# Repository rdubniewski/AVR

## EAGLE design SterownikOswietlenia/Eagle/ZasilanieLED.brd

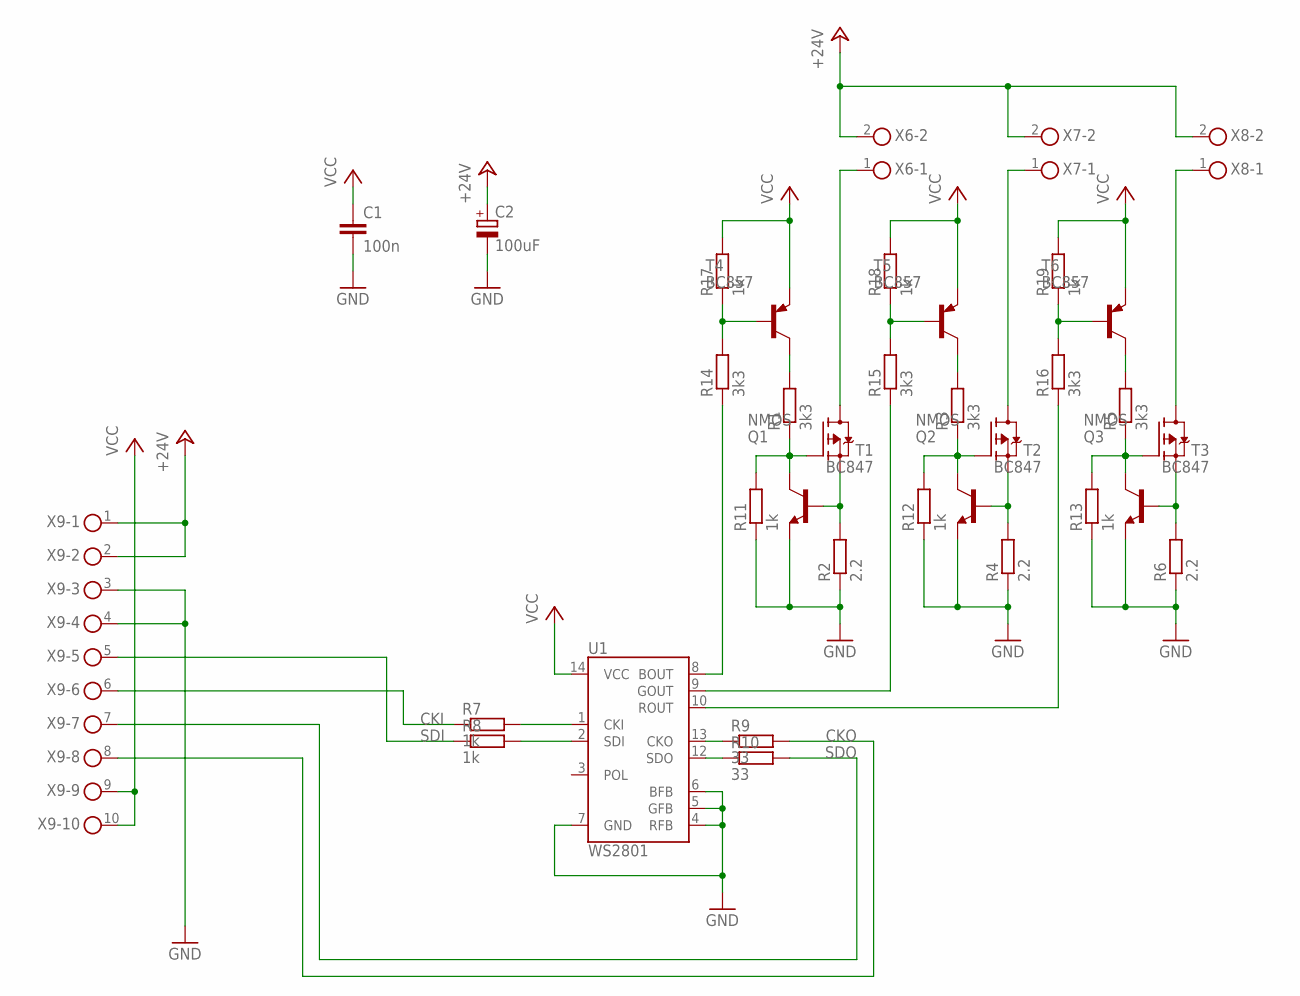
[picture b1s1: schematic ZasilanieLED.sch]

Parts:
C1: 100n; C1206
C2: 100uF; E5-10,5
Q1, Q2, Q3: NMOS; TO252
R1, R3, R5, R14, R15, R16: 3k3; R1206
R2, R4, R6: 2.2; 0207/10
R7, R8, R11, R12, R13, R17, R18, R19: 1k; R1206
R9, R10: 33; R1206
T1, T2, T3: BC847; SOT23
T4, T5, T6: BC857; SOT23-BEC
U1: WS2801; SOP-14
X6, X7, X8: AKL59-02; 2POL35
X9: AKL59-10; 10POL35

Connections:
+24V: C2.+, X6.2, X7.2, X8.2, X9.1, X9.2
CKI: R7.1, X9.6
CKO: R9.2, X9.8
GND: C1.2, C2.-, R2.1, R4.1, R6.1, R11.1, R12.1, R13.1, T1.2 (E), T2.2 (E), T3.2 (E), U1.4 (RFB), U1.5 (GFB), U1.6 (BFB), U1.7 (GND), X9.3, X9.4
unnamed: R7.2, U1.1 (CKI)
unnamed: R8.2, U1.2 (SDI)
unnamed: R9.1, U1.13 (CKO)
unnamed: R14.1, U1.8 (BOUT)
unnamed: R15.1, U1.9 (GOUT)
unnamed: R16.1, U1.10 (ROUT)
unnamed: Q1.2 (S), R2.2, T1.1 (B)
unnamed: Q2.2 (S), R4.2, T2.1 (B)
unnamed: Q3.2 (S), R6.2, T3.1 (B)
unnamed: R10.1, U1.12 (SDO)
unnamed: Q1.3 (D), X6.1
unnamed: Q2.3 (D), X7.1
unnamed: Q3.3 (D), X8.1
unnamed: R1.2, T4.C
unnamed: R3.2, T5.C
unnamed: R5.2, T6.C
unnamed: Q1.1 (G), R1.1, R11.2, T1.3 (C)
unnamed: Q2.1 (G), R3.1, R12.2, T2.3 (C)
unnamed: Q3.1 (G), R5.1, R13.2, T3.3 (C)
unnamed: R14.2, R17.1, T4.B
unnamed: R15.2, R18.1, T5.B
unnamed: R16.2, R19.1, T6.B
SDI: R8.1, X9.5
SDO: R10.2, X9.7
VCC: C1.1, R17.2, R18.2, R19.2, T4.E, T5.E, T6.E, U1.14 (VCC), X9.9, X9.10

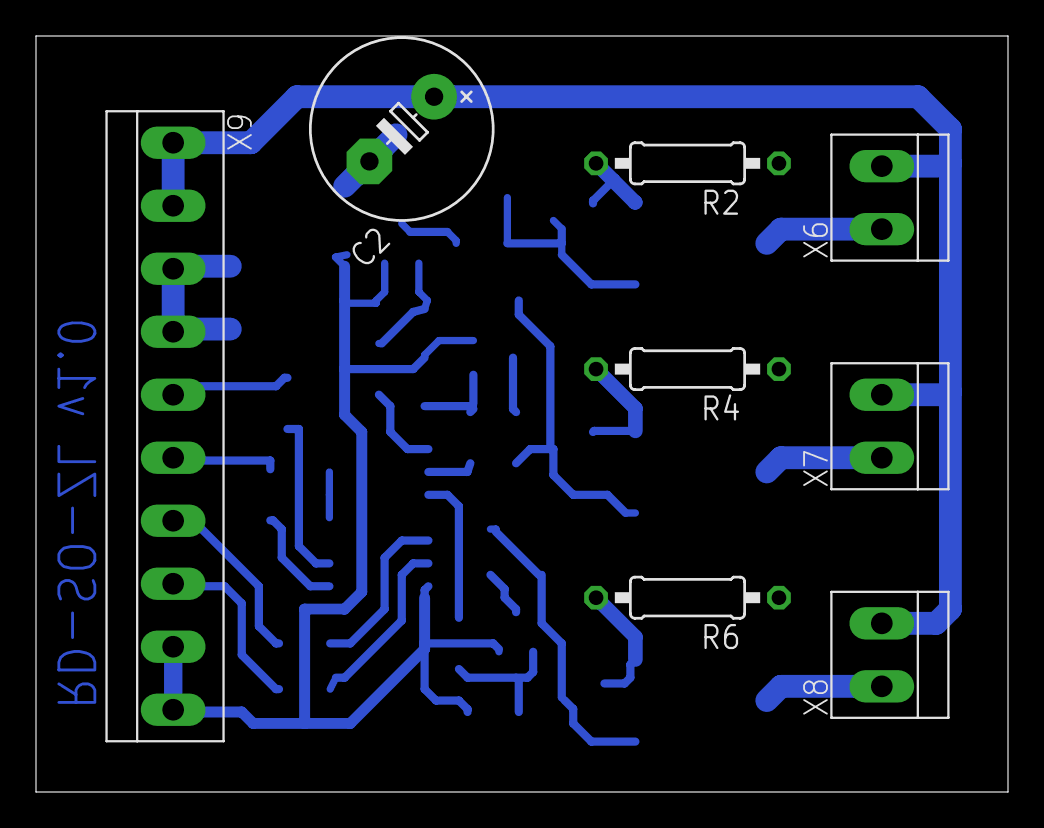
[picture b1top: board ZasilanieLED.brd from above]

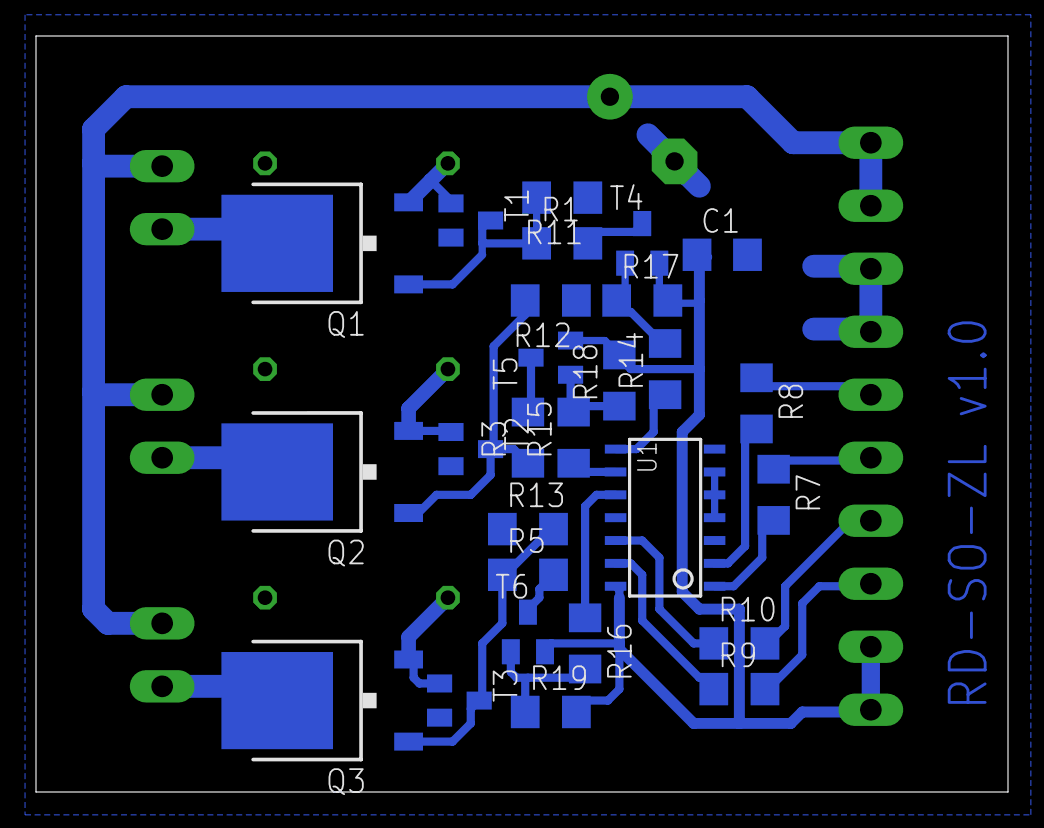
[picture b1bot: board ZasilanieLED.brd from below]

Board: 2 copper layers, 54.0 x 42.0 mm, 35 parts (27 on the bottom side), 29 nets.

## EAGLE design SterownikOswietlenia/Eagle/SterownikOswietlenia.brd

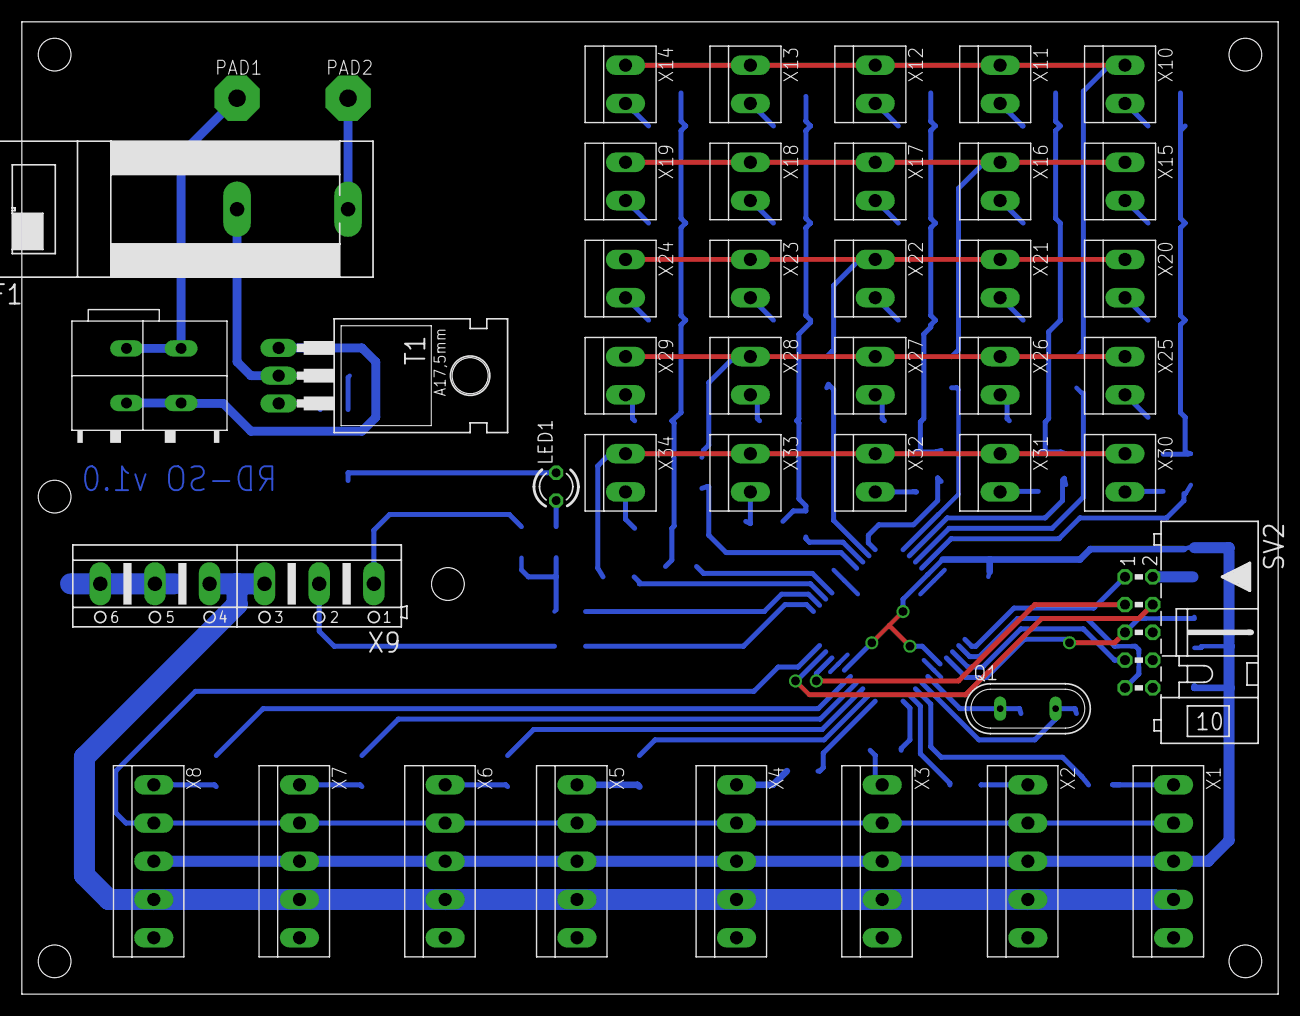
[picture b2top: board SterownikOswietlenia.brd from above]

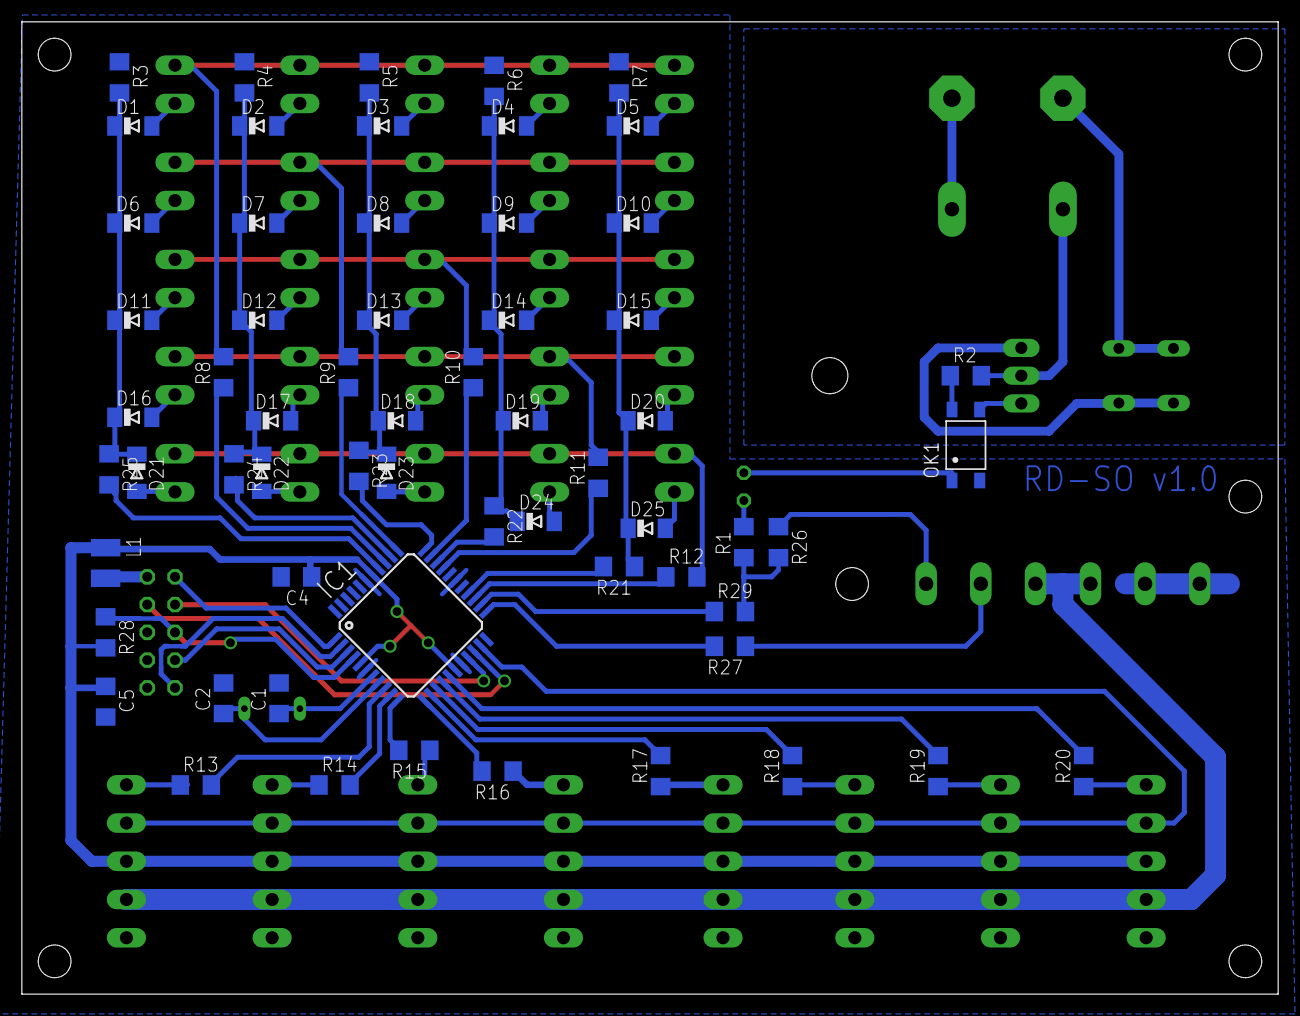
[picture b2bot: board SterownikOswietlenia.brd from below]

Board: 2 copper layers, 115.0 x 89.0 mm, 103 parts (61 on the bottom side), 87 nets.

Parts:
C1, C2: 22p; C1206
C4, C5: 100n; C1206
D1, D2, D3, D4, D5, D6, D7, D8, D9, D10, D11, D12, D13, D14, D15, D16, D17, D18, D19, D20, D21, D22, D23, D24, D25: 1N4148; MINIMELF
F1: 100mA; F457
IC1: MEGA32-A; TQFP44
L1: 100u; R1210
LED1: RED; LED3MM
OK1: TLP161J; MFP4
PAD1, PAD2: WIREPAD4,16O1,6; 4,16O1,6
Q1: 12MHz; QS
R1, R2, R8, R9, R10, R11, R12, R13, R14, R15, R16, R17, R18, R19, R20, R21, R22, R23, R24, R25, R26, R27, R29: 100; R1206
R3, R4, R5, R6, R7: 1k; R1206
R28: 10k; R1206
SV2: KANDA; ML10L
T1: BT138-H; TO220BH
U$1: AK3001-2
X1, X2, X3, X4, X5, X6, X7, X8: 5POL35
X9: AK500/6
X10, X11, X12, X13, X14, X15, X16, X17, X18, X19, X20, X21, X22, X23, X24, X25, X26, X27, X28, X29, X30, X31, X32, X33, X34: 2POL35

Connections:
+5V: L1.2, SV2.2
+24V: X1.4, X2.4, X3.4, X4.4, X5.4, X6.4, X7.4, X8.4, X9.3, X9.4
BTN-H-0: IC1.36, R8.1
BTN-H-1: IC1.34, R9.1
BTN-H-2: IC1.32, R10.1
BTN-H-3: IC1.30, R11.1
BTN-H-4: IC1.25, R12.1
BTN-V-0: IC1.37, R25.2
BTN-V-1: IC1.35, R24.2
BTN-V-2: IC1.33, R23.2
BTN-V-3: IC1.31, R22.2
BTN-V-4: IC1.26, R21.2
GND: C1.2, C2.2, C4.2, C5.2, IC1.6, IC1.18, IC1.28, IC1.39, OK1.3, R3.1, R4.1, R5.1, R6.1, R7.1, SV2.8, SV2.10, X1.5, X2.5, X3.5, X4.5, X5.5, X6.5, X7.5, X8.5, X9.5, X9.6
I2C-SCL: IC1.19, SV2.3
I2C-SDA: IC1.20, SV2.4
ISP-MISO: IC1.2, SV2.9
ISP-MOSI: IC1.1, SV2.1
ISP-SCK: IC1.3, SV2.7
LED-CKO-0: IC1.9, R13.2
LED-CKO-1: IC1.10, R14.2
LED-CKO-2: IC1.11, R15.2
LED-CKO-3: IC1.12, R16.2
LED-CKO-4: IC1.13, R17.2
LED-CKO-5: IC1.14, R18.2
LED-CKO-6: IC1.15, R19.2
LED-CKO-7: IC1.16, R20.2
LED-POWER: R1.1, R26.2, R29.2
LED-SDO: IC1.21, X1.2, X2.2, X3.2, X4.2, X5.2, X6.2, X7.2, X8.2
M$44: R12.2, X30.1, X31.1, X32.1, X33.1, X34.1
unnamed: PAD1.1, U$1.P$3, U$1.P$4
unnamed: OK1.6, R2.1
unnamed: F1.1, R2.2, T1.T2
unnamed: OK1.4, T1.G
unnamed: LED1.K, OK1.1
unnamed: LED1.A, R1.2
unnamed: R13.1, X1.1
unnamed: T1.T1, U$1.P$1, U$1.P$2
unnamed: D1.A, X10.2
unnamed: D2.A, X11.2
unnamed: F1.2, PAD2.1
unnamed: D3.A, X12.2
unnamed: D4.A, X13.2
unnamed: R14.1, X2.1
unnamed: R15.1, X3.1
unnamed: R16.1, X4.1
unnamed: R17.1, X5.1
unnamed: D5.A, X14.2
unnamed: D10.A, X19.2
unnamed: D9.A, X18.2
unnamed: D8.A, X17.2
unnamed: D7.A, X16.2
unnamed: D6.A, X15.2
unnamed: D11.A, X20.2
unnamed: D12.A, X21.2
unnamed: D13.A, X22.2
unnamed: D14.A, X23.2
unnamed: D15.A, X24.2
unnamed: D20.A, X29.2
unnamed: D19.A, X28.2
unnamed: D17.A, X26.2
unnamed: D16.A, X25.2
unnamed: D21.A, X30.2
unnamed: D22.A, X31.2
unnamed: D23.A, X32.2
unnamed: D24.A, X33.2
unnamed: D25.A, X34.2
unnamed: R18.1, X6.1
unnamed: R8.2, X10.1, X11.1, X12.1, X13.1, X14.1
unnamed: R9.2, X15.1, X16.1, X17.1, X18.1, X19.1
unnamed: R10.2, X20.1, X21.1, X22.1, X23.1, X24.1
unnamed: R11.2, X25.1, X26.1, X27.1, X28.1, X29.1
unnamed: R19.1, X7.1
unnamed: R20.1, X8.1
unnamed: C1.1, IC1.7, Q1.1
unnamed: C2.1, IC1.8, Q1.2
unnamed: R27.1, X9.2
unnamed: R26.1, X9.1
unnamed: IC1.24, R29.1
unnamed: D18.A, X27.2
unnamed: D5.C, D10.C, D15.C, D20.C, D25.C, R7.2, R21.1
unnamed: D4.C, D9.C, D14.C, D19.C, D24.C, R6.2, R22.1
unnamed: D3.C, D8.C, D13.C, D18.C, D23.C, R5.2, R23.1
unnamed: D2.C, D7.C, D12.C, D17.C, D22.C, R4.2, R24.1
unnamed: D1.C, D6.C, D11.C, D16.C, D21.C, R3.2, R25.1
POWER-IO-0: IC1.23, R27.2
RESET: IC1.4, R28.1, SV2.5
VCC: C4.1, C5.1, IC1.5, IC1.17, IC1.38, L1.1, R28.2, X1.3, X2.3, X3.3, X4.3, X5.3, X6.3, X7.3, X8.3

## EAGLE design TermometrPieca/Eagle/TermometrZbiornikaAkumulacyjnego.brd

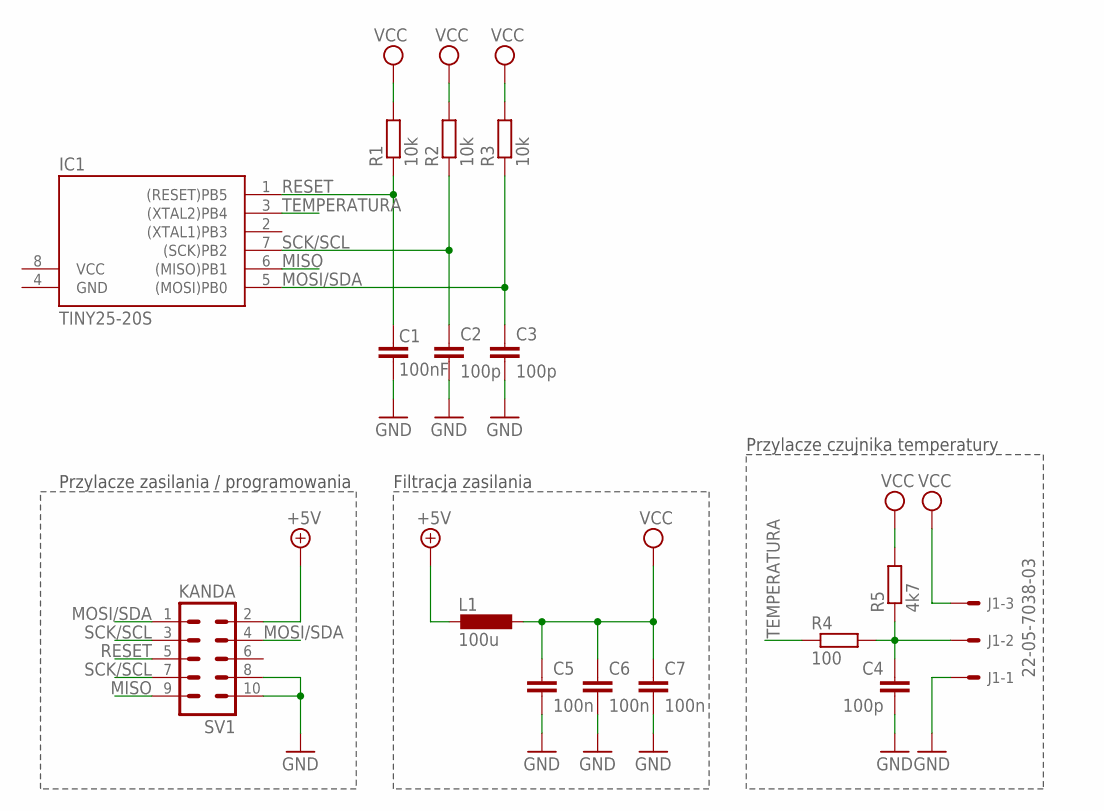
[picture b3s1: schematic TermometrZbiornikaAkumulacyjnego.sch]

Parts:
C1: 100nF; C1206
C2, C3, C4: 100p; C1206
C5, C6, C7: 100n; C1206
IC1: TINY25-20S; SOIC8
J1: 22-05-7038-03; 7395-03
L1: 100u; R1210
R1, R2, R3: 10k; R1206
R4: 100; R1206
R5: 4k7; R1206
SV1: KANDA; ML10L

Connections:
+5V: L1.2, SV1.2
GND: C1.2, C2.2, C3.2, C4.2, C5.2, C6.2, C7.2, IC1.4 (GND), J1.1, SV1.8, SV1.10
MISO: IC1.6 ((MISO)PB1), SV1.9
MOSI/SDA: C3.1, IC1.5 ((MOSI)PB0), R3.1, SV1.1, SV1.4
unnamed: C4.1, J1.2, R4.2, R5.1
RESET: C1.1, IC1.1 ((RESET)PB5), R1.1, SV1.5
SCK/SCL: C2.1, IC1.7 ((SCK)PB2), R2.1, SV1.3, SV1.7
TEMPERATURA: IC1.3 ((XTAL2)PB4), R4.1
VCC: C5.1, C6.1, C7.1, IC1.8 (VCC), J1.3, L1.1, R1.2, R2.2, R3.2, R5.2

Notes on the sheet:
Filtracja zasilania
Przylacze czujnika temperatury
Przylacze zasilania / programowania

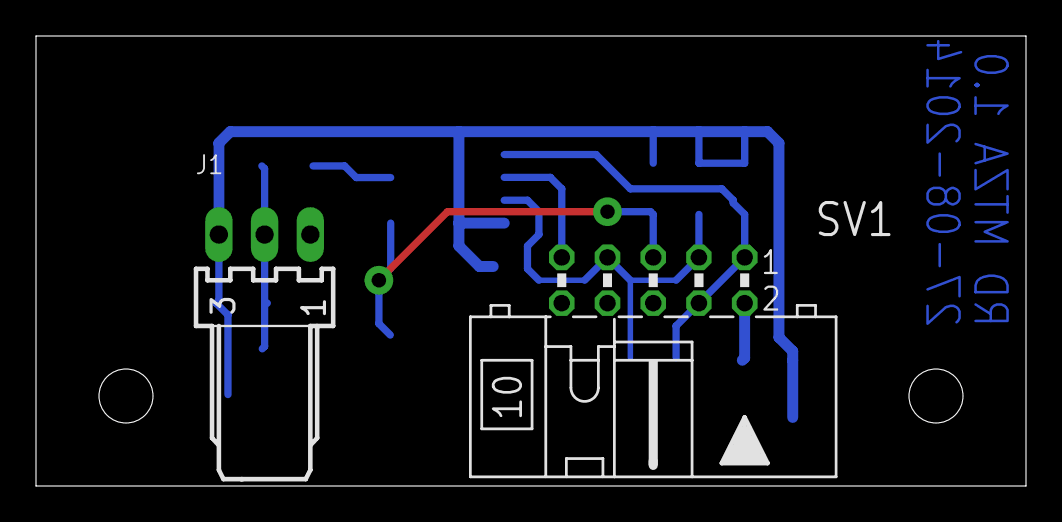
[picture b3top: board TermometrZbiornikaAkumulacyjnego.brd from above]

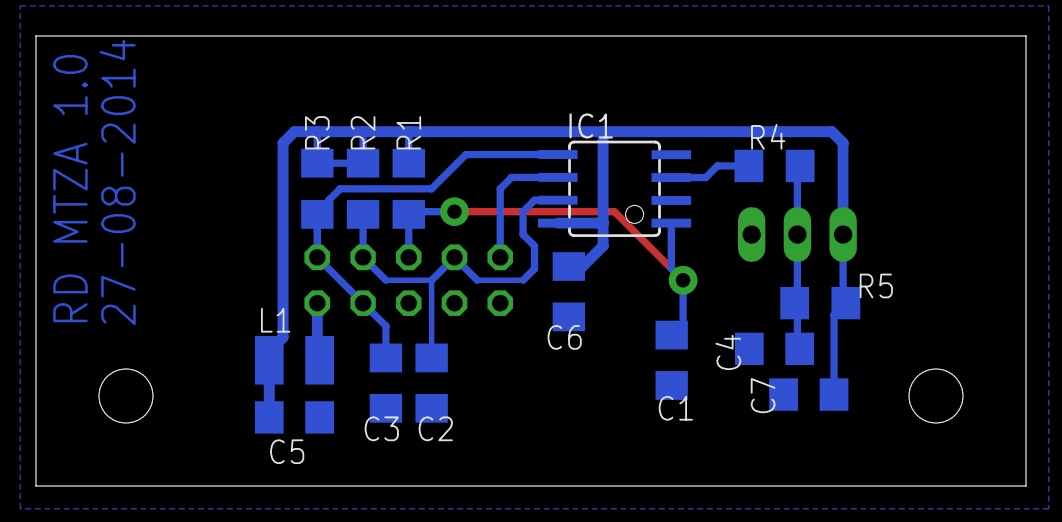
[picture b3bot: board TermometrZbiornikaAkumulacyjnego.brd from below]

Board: 2 copper layers, 55.0 x 25.0 mm, 16 parts (14 on the bottom side), 9 nets.

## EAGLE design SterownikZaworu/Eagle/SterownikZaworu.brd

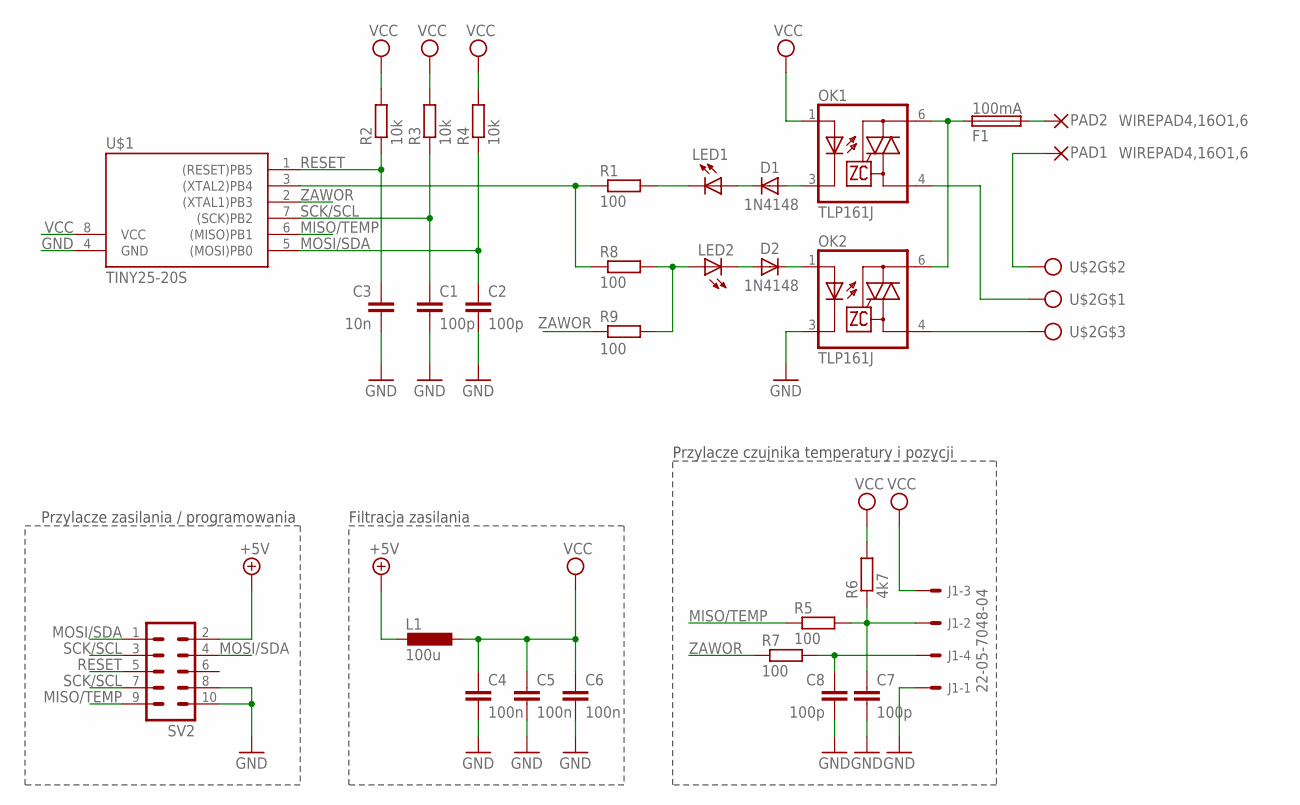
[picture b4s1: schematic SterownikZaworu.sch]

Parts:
C1, C2, C7, C8: 100p; C1206
C3: 10n; C1206
C4, C5, C6: 100n; C1206
D1, D2: 1N4148; MINIMELF
F1: 100mA; F457
J1: 22-05-7048-04; 7395-04
L1: 100u; R1210
LED1, LED2: LED3MM
OK1, OK2: TLP161J; MFP4
PAD1, PAD2: WIREPAD4,16O1,6; 4,16O1,6
R1, R5, R7, R8, R9: 100; R1206
R2, R3, R4: 10k; R1206
R6: 4k7; R1206
SV2: ML10L
U$1: TINY25-20S; SOIC8
U$2: AK3001-3

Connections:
+5V: L1.2, SV2.2
GND: C1.2, C2.2, C3.2, C4.2, C5.2, C6.2, C7.2, C8.2, J1.1, OK2.3 (C), SV2.8, SV2.10, U$1.4 (GND)
MISO/TEMP: R5.1, SV2.9, U$1.6 ((MISO)PB1)
MOSI/SDA: C2.1, R4.1, SV2.1, SV2.4, U$1.5 ((MOSI)PB0)
unnamed: PAD1.1, U$2.P$3, U$2.P$4
unnamed: C7.1, J1.2, R5.2, R6.1
unnamed: F1.1, OK1.6 (A2), OK2.6 (A2)
unnamed: D1.A, OK1.3 (C)
unnamed: D1.C, LED1.A
unnamed: LED1.K (C), R1.2
unnamed: R1.1, R8.1, U$1.3 ((XTAL2)PB4)
unnamed: OK1.4 (A1), U$2.P$1, U$2.P$2
unnamed: OK2.4 (A1), U$2.P$5, U$2.P$6
unnamed: C8.1, J1.4, R7.2
unnamed: F1.2, PAD2.1
unnamed: LED2.A, R8.2, R9.1
unnamed: D2.A, LED2.K (C)
unnamed: D2.C, OK2.1 (A)
RESET: C3.1, R2.1, SV2.5, U$1.1 ((RESET)PB5)
SCK/SCL: C1.1, R3.1, SV2.3, SV2.7, U$1.7 ((SCK)PB2)
VCC: C4.1, C5.1, C6.1, J1.3, L1.1, OK1.1 (A), R2.2, R3.2, R4.2, R6.2, U$1.8 (VCC)
ZAWOR: R7.1, R9.2, U$1.2 ((XTAL1)PB3)

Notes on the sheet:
Filtracja zasilania
Przylacze czujnika temperatury i pozycji
Przylacze zasilania / programowania

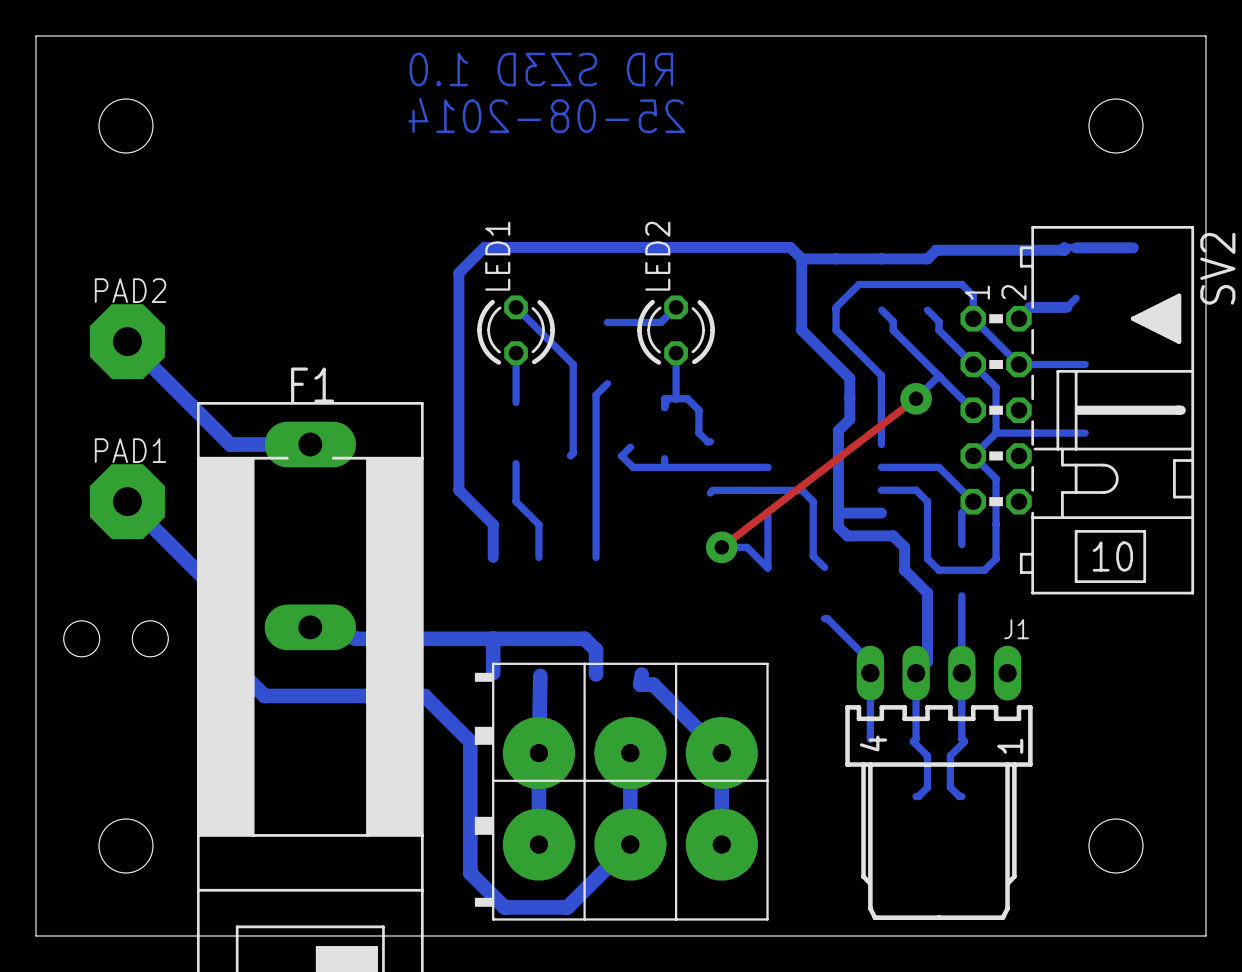
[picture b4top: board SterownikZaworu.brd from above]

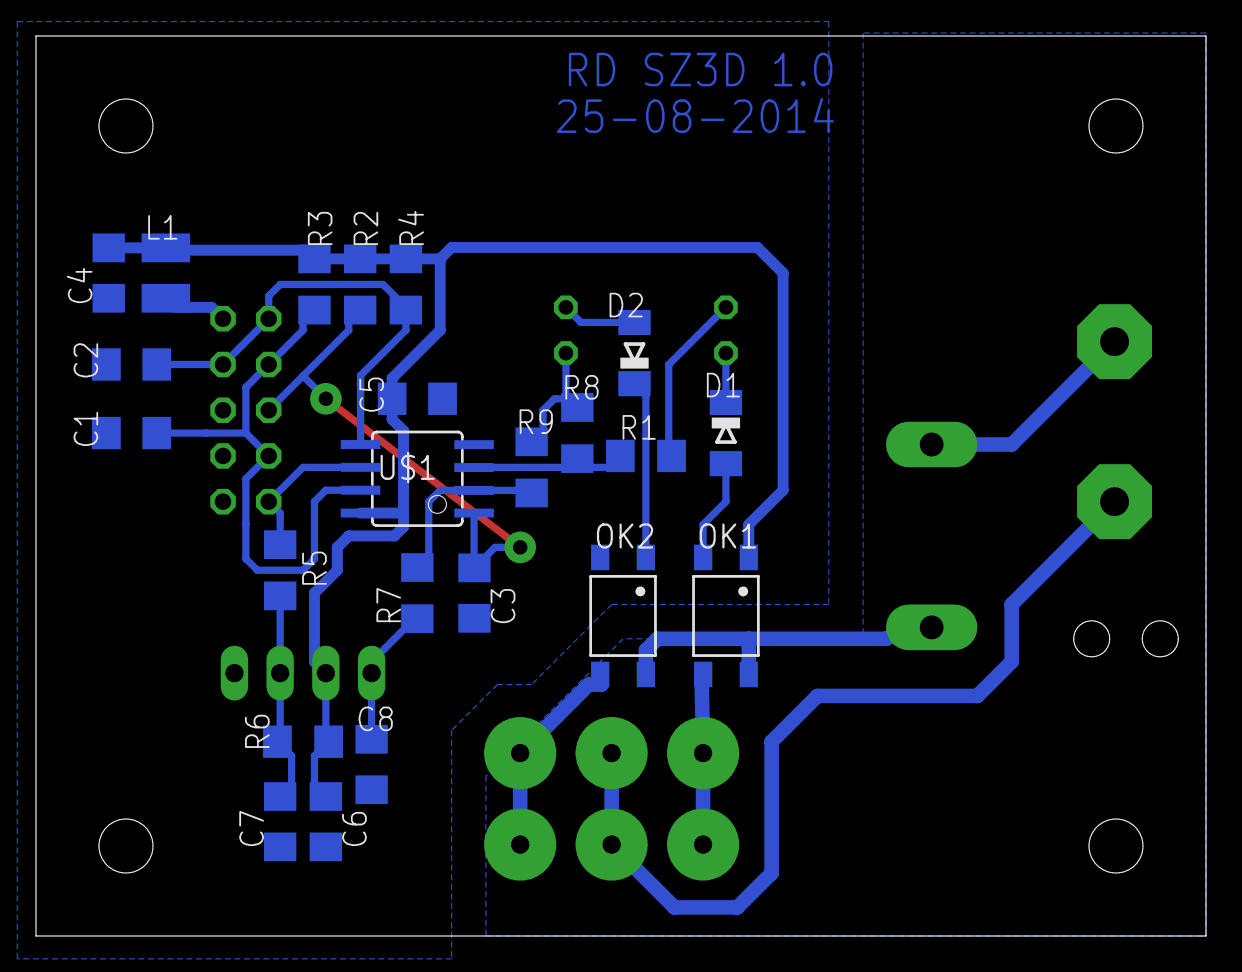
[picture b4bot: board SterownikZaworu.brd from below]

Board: 2 copper layers, 65.0 x 50.0 mm, 31 parts (23 on the bottom side), 22 nets.

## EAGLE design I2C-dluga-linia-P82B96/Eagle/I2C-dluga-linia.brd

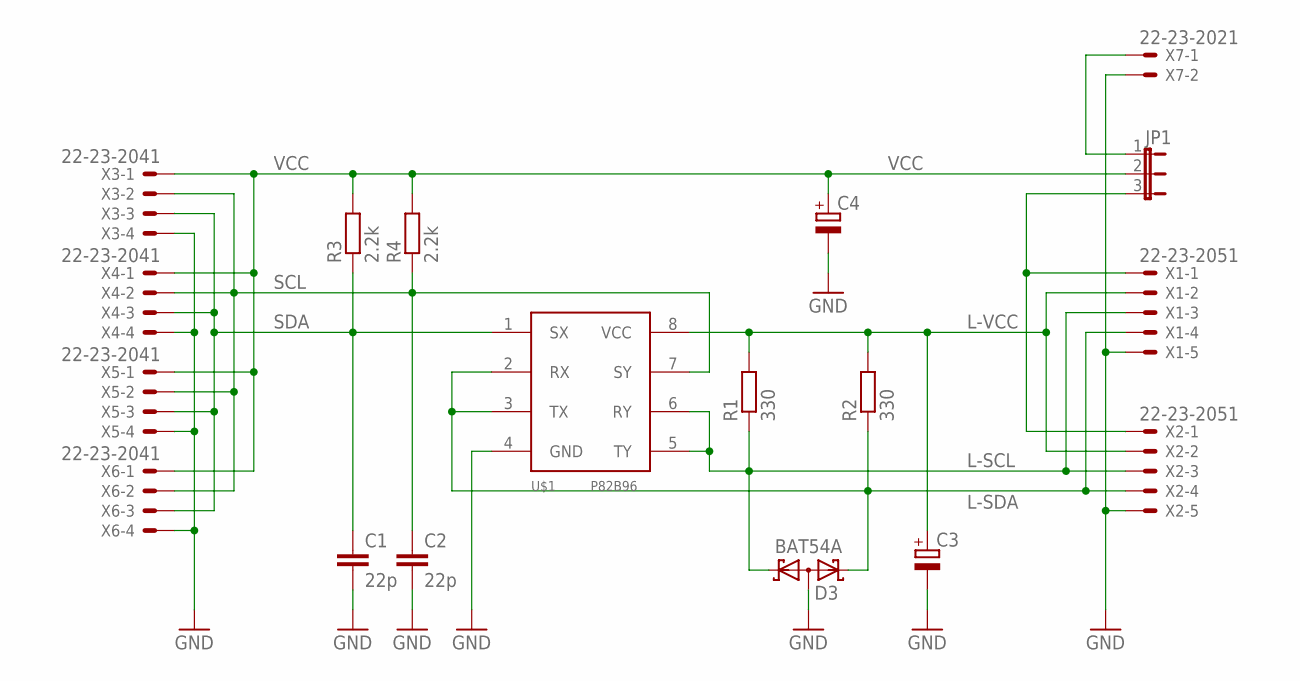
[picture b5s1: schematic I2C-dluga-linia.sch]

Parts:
C1, C2: 22p; C1206
C3: CPOL-EUE5-10.5; E5-10,5
C4: CPOL-EUE3.5-8; E3,5-8
D3: BAT54A; SOT23
JP1: JP2E; JP2
R1, R2: 330; R1206
R3, R4: 2.2k; R1206
U$1: P82B96; SOIC8
X1, X2: 22-23-2051
X3, X4, X5, X6: 22-23-2041
X7: 22-23-2021

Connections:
GND: C1.2, C2.2, C3.-, C4.-, D3.3 (AA), U$1.4 (GND), X1.5, X2.5, X3.4, X4.4, X5.4, X6.4, X7.2
L-SCL: D3.1 (K1), R1.1, U$1.5 (TY), U$1.6 (RY), X1.3, X2.3
L-SDA: D3.2 (K2), R2.1, U$1.2 (RX), U$1.3 (TX), X1.4, X2.4
L-VCC: C3.+, R1.2, R2.2, U$1.8 (VCC), X1.2, X2.2
unnamed: JP1.3, X1.1, X2.1
unnamed: JP1.1, X7.1
SCL: C2.1, R4.1, U$1.7 (SY), X3.2, X4.2, X5.2, X6.2
SDA: C1.1, R3.1, U$1.1 (SX), X3.3, X4.3, X5.3, X6.3
VCC: C4.+, JP1.2, R3.2, R4.2, X3.1, X4.1, X5.1, X6.1

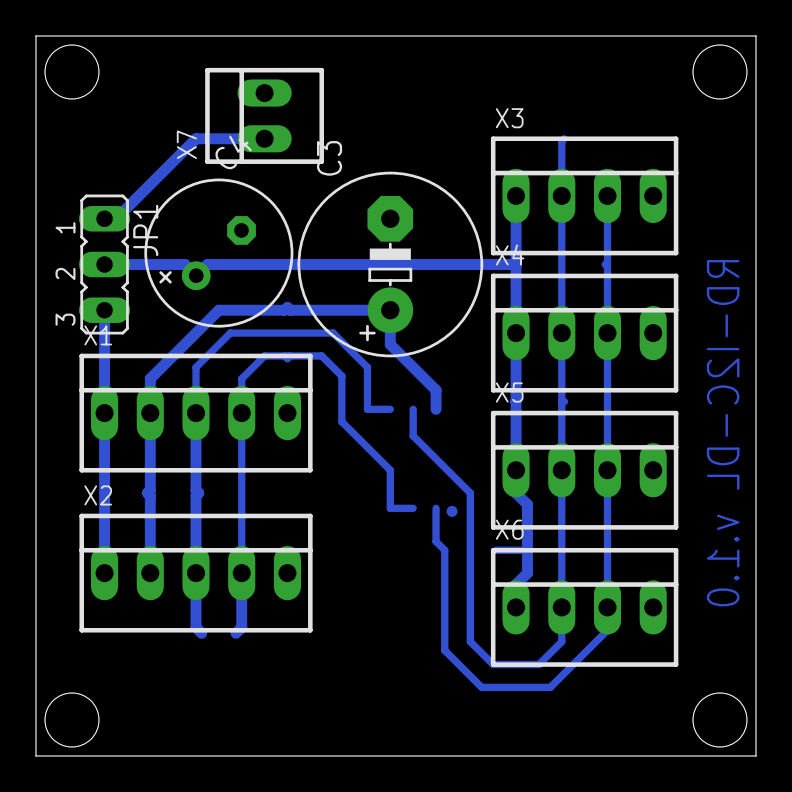
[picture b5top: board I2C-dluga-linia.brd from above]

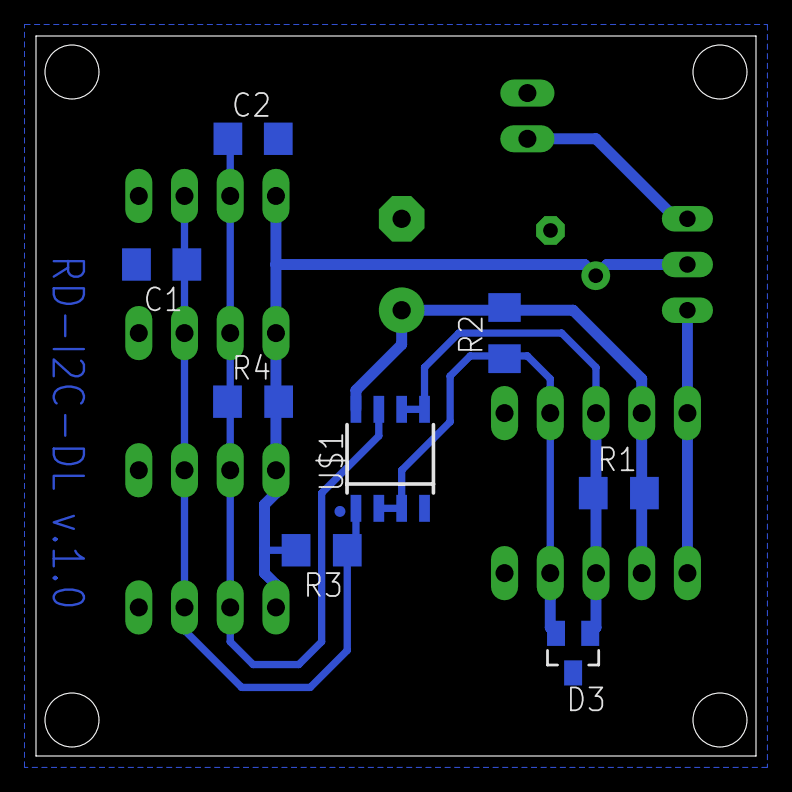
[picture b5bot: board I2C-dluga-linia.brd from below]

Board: 2 copper layers, 40.0 x 40.0 mm, 18 parts (8 on the bottom side), 9 nets.

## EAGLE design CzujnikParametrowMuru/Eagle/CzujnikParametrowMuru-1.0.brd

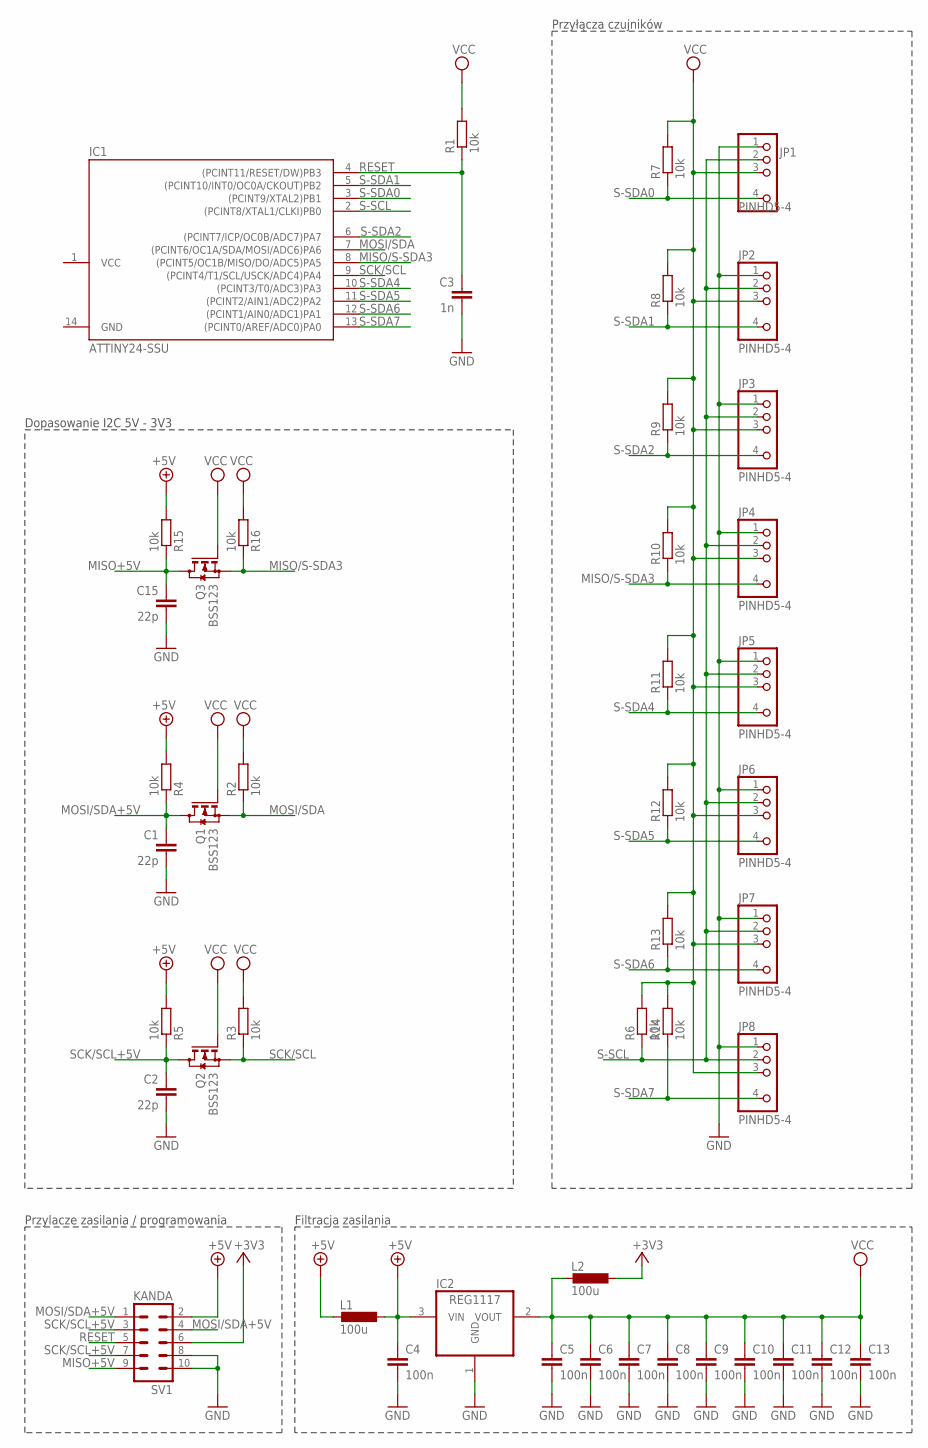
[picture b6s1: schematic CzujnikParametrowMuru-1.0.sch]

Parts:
C1, C2, C15: 22p; C1206
C3: 1n; C1206
C4, C5, C6, C7, C8, C9, C10, C11, C12, C13: 100n; C1206
IC1: ATTINY24-SSU; SOIC14
IC2: REG1117; SOT223
JP1, JP2, JP3, JP4, JP5, JP6, JP7, JP8: PINHD5-4; 1X5-4
L1, L2: 100u; R1210
Q1, Q2, Q3: BSS123; SOT23
R1, R2, R3, R4, R5, R6, R7, R8, R9, R10, R11, R12, R13, R14, R15, R16: 10k; R1206
SV1: KANDA; ML10L

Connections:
+3V3: L2.1, SV1.6
+5V: C4.1, IC2.3 (VIN), L1.1, R4.2, R5.2, R15.2
+5V_W: L1.2, SV1.2
GND: C1.2, C2.2, C3.2, C4.2, C5.2, C6.2, C7.2, C8.2, C9.2, C10.2, C11.2, C12.2, C13.2, C15.2, IC1.14 (GND), IC2.1 (GND), JP1.1, JP2.1, JP3.1, JP4.1, JP5.1, JP6.1, JP7.1, JP8.1, SV1.8, SV1.10
MISO+5V: C15.1, Q3.3 (D), R15.1, SV1.9
MISO/S-SDA3: IC1.8 ((PCINT5/OC1B/MISO/DO/ADC5)PA5), JP4.4, Q3.2 (S), R10.1, R16.1
MOSI/SDA: IC1.7 ((PCINT6/OC1A/SDA/MOSI/ADC6)PA6), Q1.2 (S), R2.1
MOSI/SDA+5V: C1.1, Q1.3 (D), R4.1, SV1.1, SV1.4
RESET: C3.1, IC1.4 ((PCINT11/RESET/DW)PB3), R1.1, SV1.5
S-SCL: IC1.2 ((PCINT8/XTAL1/CLKI)PB0), JP1.2, JP2.2, JP3.2, JP4.2, JP5.2, JP6.2, JP7.2, JP8.2, R6.1
S-SDA0: IC1.3 ((PCINT9/XTAL2)PB1), JP1.4, R7.1
S-SDA1: IC1.5 ((PCINT10/INT0/OC0A/CKOUT)PB2), JP2.4, R8.1
S-SDA2: IC1.6 ((PCINT7/ICP/OC0B/ADC7)PA7), JP3.4, R9.1
S-SDA4: IC1.10 ((PCINT3/T0/ADC3)PA3), JP5.4, R11.1
S-SDA5: IC1.11 ((PCINT2/AIN1/ADC2)PA2), JP6.4, R12.1
S-SDA6: IC1.12 ((PCINT1/AIN0/ADC1)PA1), JP7.4, R13.1
S-SDA7: IC1.13 ((PCINT0/AREF/ADC0)PA0), JP8.4, R14.1
SCK/SCL: IC1.9 ((PCINT4/T1/SCL/USCK/ADC4)PA4), Q2.2 (S), R3.1
SCK/SCL+5V: C2.1, Q2.3 (D), R5.1, SV1.3, SV1.7
VCC: C5.1, C6.1, C7.1, C8.1, C9.1, C10.1, C11.1, C12.1, C13.1, IC1.1 (VCC), IC2.2 (VOUT), JP1.3, JP2.3, JP3.3, JP4.3, JP5.3, JP6.3, JP7.3, JP8.3, L2.2, Q1.1 (G), Q2.1 (G), Q3.1 (G), R1.2, R2.2, R3.2, R6.2, R7.2, R8.2, R9.2, R10.2, R11.2, R12.2, R13.2, R14.2, R16.2

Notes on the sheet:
Filtracja zasilania
Przylacze zasilania / programowania
Dopasowanie I2C 5V - 3V3
Przyłącza czujników

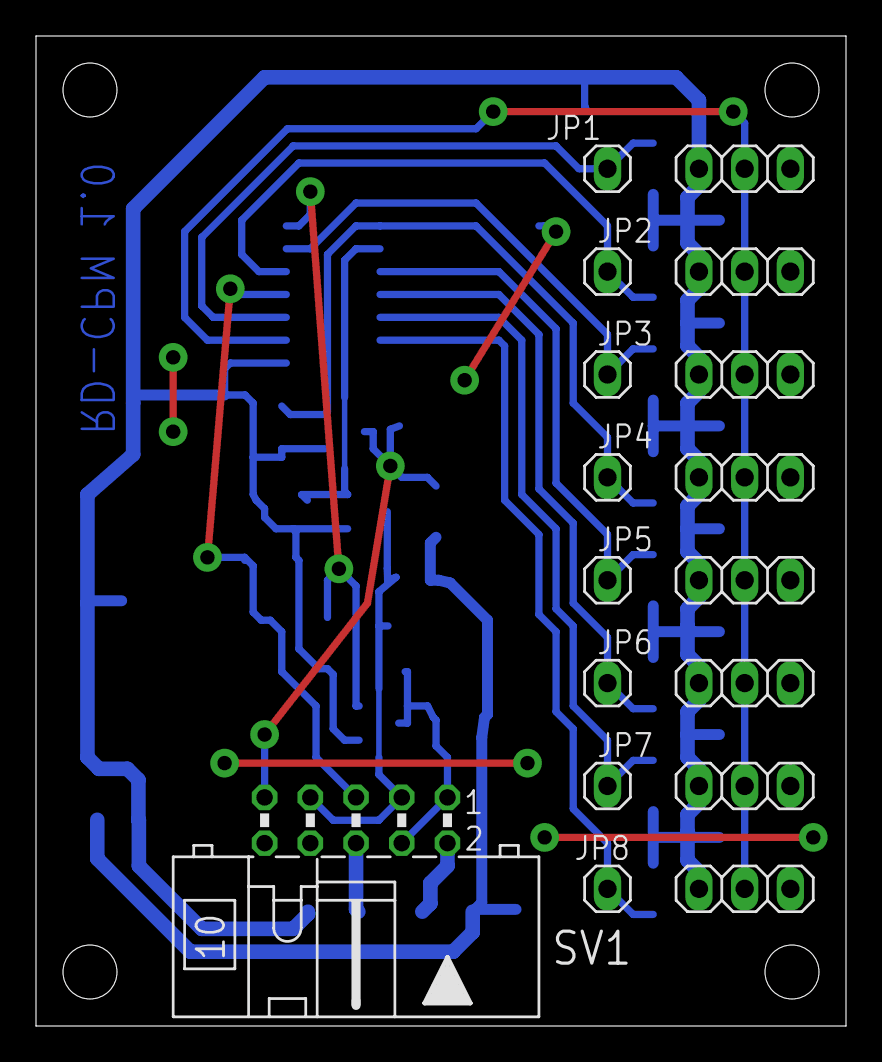
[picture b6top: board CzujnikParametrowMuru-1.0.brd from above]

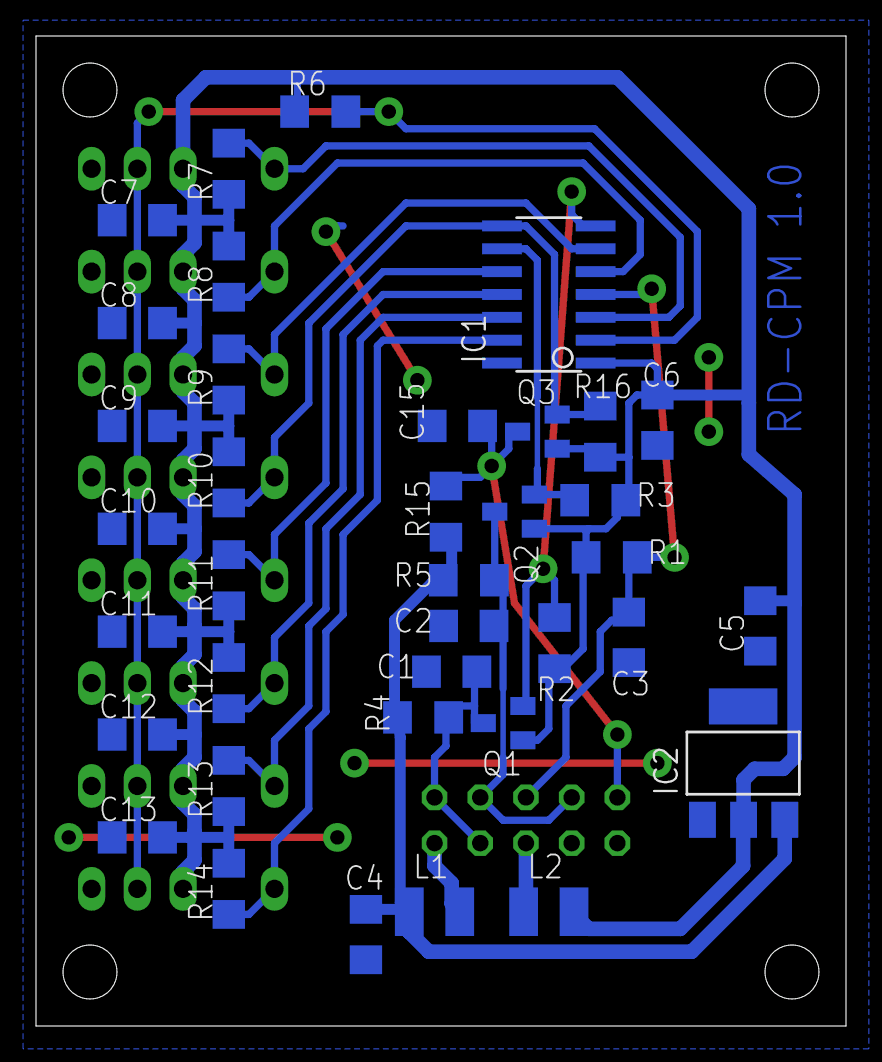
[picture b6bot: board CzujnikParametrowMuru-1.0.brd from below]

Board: 2 copper layers, 45.0 x 55.0 mm, 46 parts (37 on the bottom side), 20 nets.

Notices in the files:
parts and their libraries:
SparkFun: Licensing: CC v3.0 Share-Alike You are welcome to use this library for commercial purposes.
